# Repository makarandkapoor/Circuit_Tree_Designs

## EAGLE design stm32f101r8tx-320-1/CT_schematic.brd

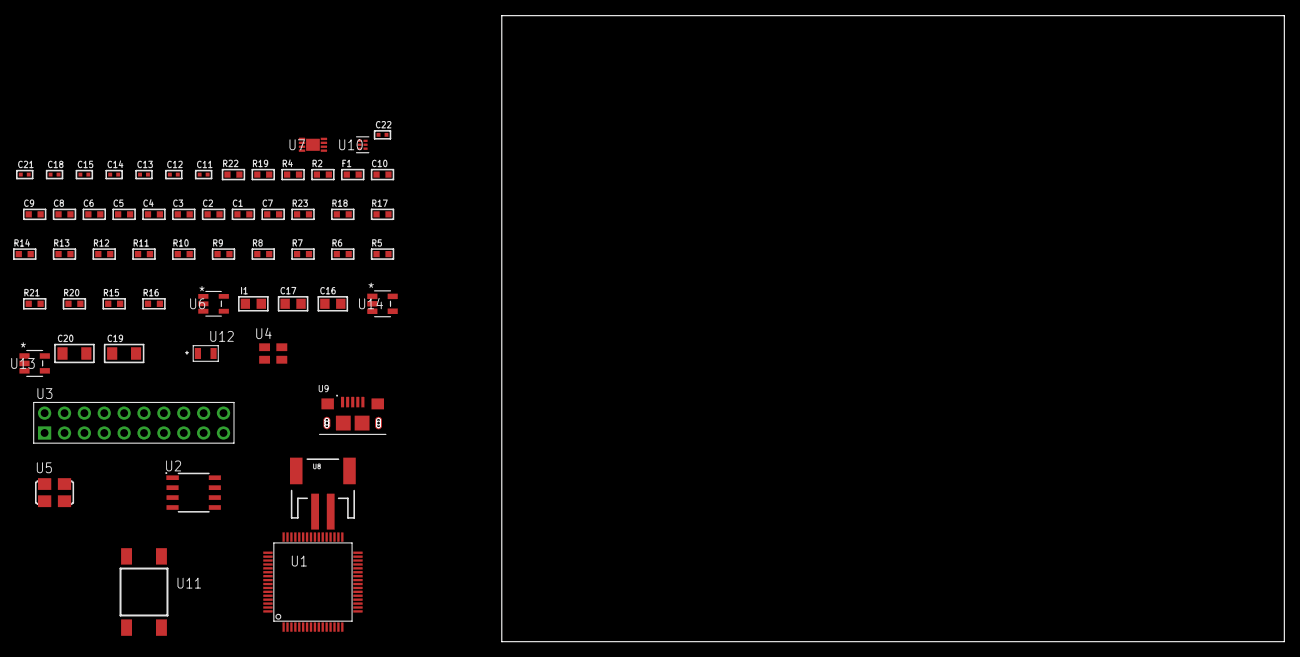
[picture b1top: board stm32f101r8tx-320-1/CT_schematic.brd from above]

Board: 2 copper layers, 122.6 x 80.0 mm, 59 parts (0 on the bottom side), 32 nets, no tracks yet.

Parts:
C1, C10: 1e-06; C0603
C2, C3, C4, C5, C6: 1e-07; C0603
C7: 4.7e-06; C0603
C8, C9: 1e-08; C0603
C11, C14, C15, C21, C22: 1e-08; C0402
C12, C13, C18: 1e-07; C0402
C16, C17: 1e-05; C0805
C19, C20: 1e-05; C1206
F1: 240.0; L0603
I1: 2.2e-06; L0805
R2: 1000.0; R0603
R4: 4700.0; R0603
R5, R6, R7, R8, R9, R10, R11, R12, R13, R14, R17, R18, R23: 10000.0; R0603
R15: 220000.0; R0603
R16: 1000000.0; R0603
R19: 9100.0; R0603
R20: 680000.0; R0603
R21: 120000.0; R0603
R22: 2000.0; R0603
U1: STM32F101R8T6; LQFP64
U2: AT25040B-SSHL-T; SOIC-8
U3: TST-110-05-T-D-RA
U4: ASEK-32.768KHz-ECST; ASEK
U5: ASFL1-25MHZ-NCS; ASFL1
U6: ltc3406es5; TSOT-23-5
U7: MCP73831T-2ACI/MC; DFN8_2X3MC
U8: S2B-PH-SM4-TB(LF)(SN); JST-2-SMD
U9: 10118193-0001LF; FCI_10118193-0001LF
U10: TPS3895ADRYR; SON-6
U11: 4-1437565-2; SW_4-1437565-2
U12: Q65110A2395; LGM67K-G1J2-24-Z
U13, U14: nc7sz125m5x; NC7SZ125M5X

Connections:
CLK_U1_3: U1.3, U4.3
CLK_U1_5: U1.5, U5.3
GND: C1.2, C2.2, C3.2, C4.2, C5.2, C6.2, C7.2, C8.2, C9.2, C10.2, C11.2, C12.2, C13.2, C14.2, C15.2, C16.2, C17.1, C17.2, C18.2, C19.2, C20.2, C21.2, C22.2, R2.2, R5.2, R14.2, R15.2, R19.2, R21.2, R22.2, U1.12, U1.18, U1.31, U1.47, U1.63, U2.4, U3.4, U3.6, U3.8, U3.10, U3.12, U3.14, U3.16, U3.18, U3.20, U4.2, U5.2, U6.2, U7.6, U7.9, U8.2, U9.5, U9.6, U9.7, U9.8, U9.9, U10.2, U12.C, U13.2, U13.3, U14.1, U14.3
INPUT_USBPOWER_5V: C19.1, R23.2, U7.1, U7.2, U9.1
NET_U1_7: R4.1, U1.7, U14.4
NET_U1_13: C8.1, C9.1, C10.1, F1.1, U1.13
NET_U1_60: R5.1, U1.60
NET_U1_62: U11.3, U11.4
NET_U2_3: R6.1, U2.3
NET_U2_7: R8.1, U2.7
NET_U3_3: R9.1, U3.3
NET_U3_7: R11.1, U3.7
NET_U3_9: R12.1, U3.9
NET_U3_19: R14.1, U3.19
NET_U6_3: I1.1, U6.3
NET_U6_5: R15.1, R16.1, U6.5
NET_U6_ATNET_3: I1.2, R16.2
NET_U7_5: R23.1, U7.5
NET_U7_8: R22.1, U7.8
NET_U10_1: R18.1, R19.1, U10.1
NET_U10_3: R20.2, R21.1, U10.3
NET_U10_4: R17.1, U10.4, U13.4, U14.2
NET_U11_1: R2.1, U11.1, U11.2
PROC_SPI1_MISO: U1.22, U2.2
PROC_SPI1_MOSI: U1.23, U2.5
PROC_SPI1_NSS: R7.1, U1.20, U2.1
PROC_SPI1_SCK: U1.21, U2.6
PROC_SYS_JTDI: R10.1, U1.50, U3.5
PROC_SYS_JTDO_TRACESWO: U1.55, U3.13
RST_OUT_U3_SRESET_B: R13.1, U3.15, U13.1
VCC_S1_3V7: C16.1, C20.1, U6.4, U7.3, U7.4, U8.1
VCC_TIER1_3V3: C1.1, C2.1, C3.1, C4.1, C5.1, C6.1, C7.1, C11.1, C12.1, C13.1, C14.1, C15.1, C17.2, C18.1, C21.1, C22.1, F1.2, I1.2, R4.2, R6.2, R7.2, R8.2, R9.2, R10.2, R11.2, R12.2, R13.2, R16.2, R17.2, R18.2, R20.1, U1.1, U1.19, U1.32, U1.48, U1.64, U2.8, U3.1, U3.2, U4.4, U5.4, U10.6, U13.5, U14.5

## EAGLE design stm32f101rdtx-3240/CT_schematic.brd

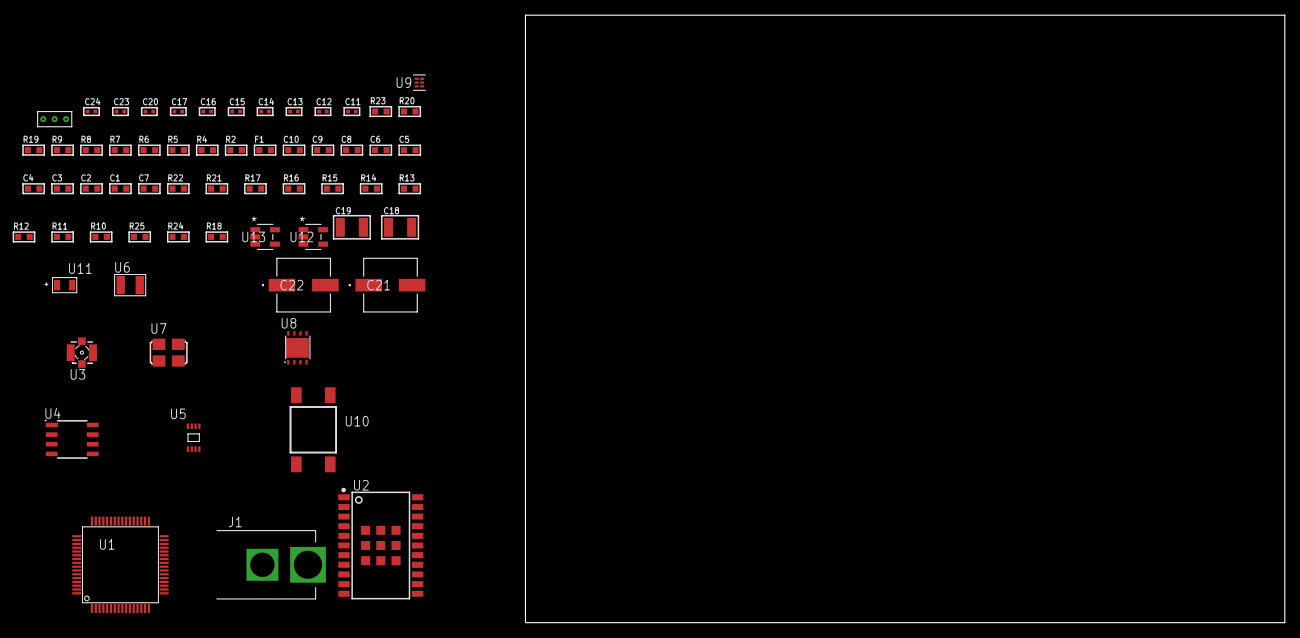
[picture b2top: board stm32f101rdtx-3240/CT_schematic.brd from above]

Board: 2 copper layers, 100.0 x 80.0 mm, 63 parts (0 on the bottom side), 37 nets, no tracks yet.

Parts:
C1, C10: 1e-06; C0603
C2, C3, C4, C5, C6: 1e-07; C0603
C7: 4.7e-06; C0603
C8, C9: 1e-08; C0603
C11, C12: 1e-11; C0402
C13, C20: 1e-07; C0402
C14, C15, C16, C17, C23, C24: 1e-08; C0402
C18, C19: 1e-05; C1210
C21, C22: 0.0001; EXV-9H
F1: 240.0; L0603
J1: PJ-037B; PJ-037B_PACKAGE
R2, R20: 1000.0; R0603
R4, R5: 4700.0; R0603
R6, R7, R8, R9: 2200.0; R0603
R10, R11, R12, R13, R14, R15, R16, R17, R21, R22: 10000.0; R0603
R18: 100000.0; R0603
R19: 2231.0; R0603
R23: 9100.0; R0603
R24: 680000.0; R0603
R25: 120000.0; R0603
U1: STM32F101RDT6; LQFP64
U2: A2200-A
U3: 73412-0114; COAXIAL_C
U4: AT25128B-SSHL-T; SOIC-8
U5: 24AA32AT-I/MNY; TDFN-8/6MM
U6: ABS07-32.768KHZ-7-T
U7: ASFL1-25MHZ-NCS; ASFL1
U8: LP3878SDX-ADJ/NOPB; WSON-8
U9: TPS3895ADRYR; SON-6
U10: 4-1437565-2; SW_4-1437565-2
U11: Q65110A2395; LGM67K-G1J2-24-Z
U12, U13: nc7sz125m5x; NC7SZ125M5X
U14: Dummy; DUMMY_PACKAGE_134

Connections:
CLK_CRYSTAL_U1_3: C11.1, U1.3, U6.1
CLK_CRYSTAL_U1_4: C12.1, U1.4, U6.2
CLK_U1_5: U1.5, U7.3
GND: C1.2, C2.2, C3.2, C4.2, C5.2, C6.2, C7.2, C8.2, C9.2, C10.2, C11.2, C12.2, C13.2, C14.2, C15.2, C16.2, C17.2, C18.2, C19.2, C20.2, C21.2, C22.2, C23.2, C24.2, J1.2, R2.2, R10.2, R17.2, R20.2, R23.2, R25.2, U1.12, U1.18, U1.31, U1.47, U1.63, U2.7, U2.8, U2.23, U2.24, U2.25, U2.26, U2.27, U2.28, U2.29, U2.30, U2.31, U4.4, U5.4, U5.7, U7.2, U8.3, U8.PAD, U9.2, U11.C, U12.1, U12.3, U13.1, U13.3, U14.1
NET_U1_7: R5.1, U1.7, U13.4
NET_U1_13: C8.1, C9.1, C10.1, F1.1, U1.13
NET_U1_29: R8.1, U1.29, U5.6
NET_U1_30: R9.1, U1.30, U5.5
NET_U1_58: R6.1, U1.58, U2.15
NET_U1_59: R7.1, U1.59, U2.16
NET_U1_60: R10.1, U1.60
NET_U1_62: U10.3, U10.4
NET_U2_2: R11.2, U2.2
NET_U2_17: R11.1, U2.17
NET_U2_22: R4.1, U2.22, U12.4
NET_U3_1: U2.11, U3.1
NET_U3_2: U2.10, U3.2, U3.3, U3.4
NET_U4_3: R12.1, U4.3
NET_U4_7: R14.1, U4.7
NET_U5_1: R15.1, U5.1
NET_U5_2: R16.1, U5.2
NET_U5_3: R17.1, U5.3
NET_U8_1: C17.1, U8.1
NET_U8_6: R19.2, R20.1, U8.6
NET_U8_8: R18.1, U8.8
NET_U9_1: R22.1, R23.1, U9.1
NET_U9_3: R24.2, R25.1, U9.3
NET_U9_4: R21.1, U9.4, U12.2, U13.2
NET_U10_1: R2.1, U10.1, U10.2
PROC_SPI1_MISO: U1.22, U4.2
PROC_SPI1_MOSI: U1.23, U4.5
PROC_SPI1_NSS: R13.1, U1.20, U4.1
PROC_SPI1_SCK: U1.21, U4.6
PROC_TIM2_CH3: U1.16, U14.3
PROC_TIM2_CH4: U1.17, U14.2
VCC_S1_13V9: C18.1, C21.1, C22.1, J1.1, R18.2, U8.4
VCC_TIER1_3V3: C1.1, C2.1, C3.1, C4.1, C5.1, C6.1, C7.1, C13.1, C14.1, C15.1, C16.1, C19.1, C20.1, C23.1, C24.1, F1.2, R4.2, R5.2, R6.2, R7.2, R8.2, R9.2, R12.2, R13.2, R14.2, R15.2, R16.2, R19.1, R21.2, R22.2, R24.1, U1.1, U1.19, U1.32, U1.48, U1.64, U2.20, U4.8, U5.8, U7.4, U8.5, U9.6, U12.5, U13.5

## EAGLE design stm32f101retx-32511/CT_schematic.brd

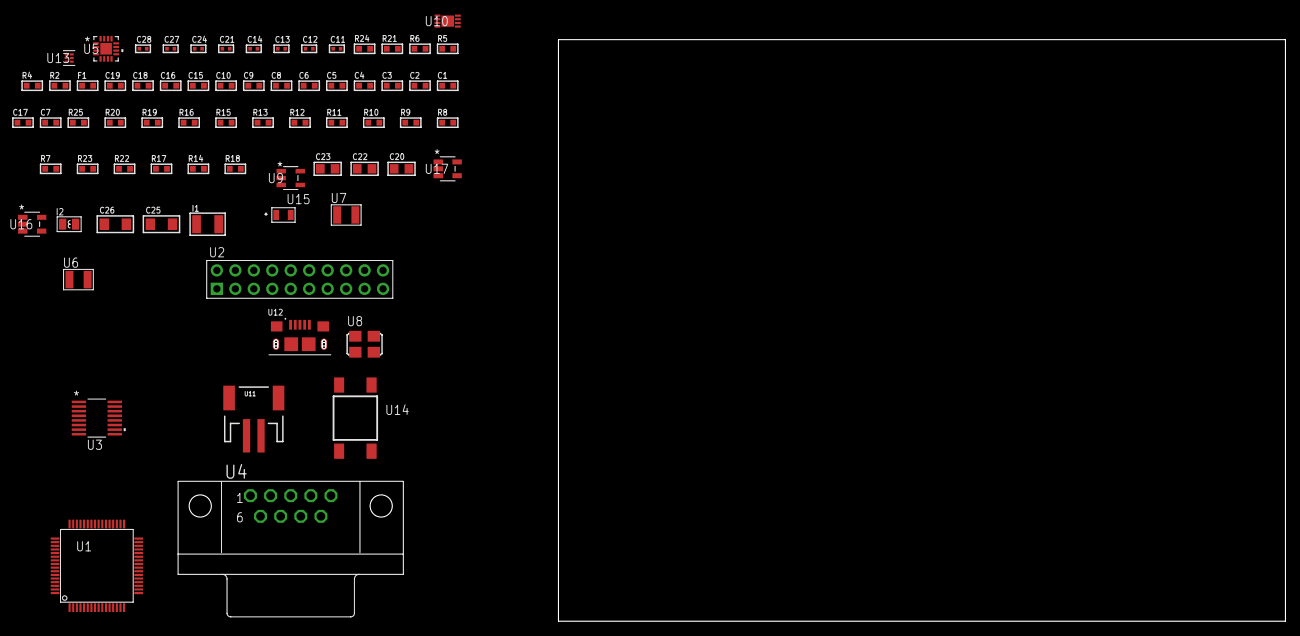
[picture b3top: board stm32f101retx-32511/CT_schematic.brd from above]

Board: 2 copper layers, 71 parts (0 on the bottom side), 44 nets, no tracks yet.

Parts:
C1, C10, C15, C16, C18, C19: 1e-06; C0603
C2, C3, C4, C5, C6: 1e-07; C0603
C7: 4.7e-06; C0603
C8, C9: 1e-08; C0603
C11, C12: 1e-11; C0402
C13, C14, C24: 1e-07; C0402
C17: 2.2e-07; C0603
C20: 4.7e-06; C0805
C21, C27, C28: 1e-08; C0402
C22, C23: 1e-05; C0805
C25, C26: 1e-05; C1206
F1: 240.0; L0603
I1: 1e-05; L1210
I2: 1.5e-06; L0806
R2: 1000.0; R0603
R4: 4700.0; R0603
R5, R6: 2200.0; R0603
R7, R8, R9, R10, R11, R12, R13, R15, R16, R19, R20, R25: 10000.0; R0603
R14: 100000.0; R0603
R17: 220000.0; R0603
R18: 1000000.0; R0603
R21: 9100.0; R0603
R22: 680000.0; R0603
R23: 120000.0; R0603
R24: 2000.0; R0603
U1: STM32F101RET6; LQFP64
U2: TST-110-05-T-D-RA
U3: LTC2804CGN-1#PBF; SSOP-16
U4: 182-009-113R531; 182-009-MALE
U5: M41T65Q6F; M41T65_QFN-16
U6, U7: ABS07-32.768KHZ-7-T
U8: ASFL1-25MHZ-NCS; ASFL1
U9: ltc3406es5; TSOT-23-5
U10: MCP73831T-2ACI/MC; DFN8_2X3MC
U11: S2B-PH-SM4-TB(LF)(SN); JST-2-SMD
U12: 10118193-0001LF; FCI_10118193-0001LF
U13: TPS3895ADRYR; SON-6
U14: 4-1437565-2; SW_4-1437565-2
U15: Q65110A2395; LGM67K-G1J2-24-Z
U16, U17: nc7sz125m5x; NC7SZ125M5X

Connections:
CLK_CRYSTAL_U1_3: C11.1, U1.3, U7.1
CLK_CRYSTAL_U1_4: C12.1, U1.4, U7.2
CLK_CRYSTAL_U5_1: U5.1, U6.1
CLK_CRYSTAL_U5_2: U5.2, U6.2
CLK_U1_5: U1.5, U8.3
GND: C1.2, C2.2, C3.2, C4.2, C5.2, C6.2, C7.2, C8.2, C9.2, C10.2, C11.2, C12.2, C13.2, C14.2, C15.2, C16.2, C18.2, C19.2, C20.2, C21.2, C22.2, C23.1, C23.2, C24.2, C25.2, C26.2, C27.2, C28.2, R2.2, R7.2, R13.2, R17.2, R21.2, R23.2, R24.2, U1.12, U1.18, U1.31, U1.47, U1.63, U2.4, U2.6, U2.8, U2.10, U2.12, U2.14, U2.16, U2.18, U2.20, U3.8, U4.5, U5.3, U5.5, U5.17, U8.2, U9.2, U10.6, U10.9, U11.2, U12.5, U12.6, U12.7, U12.8, U12.9, U13.2, U15.C, U16.2, U16.3, U17.1, U17.3
INPUT_USBPOWER_5V: C25.1, R25.2, U10.1, U10.2, U12.1
NET_U1_7: R4.1, U1.7, U17.4
NET_U1_13: C8.1, C9.1, C10.1, F1.1, U1.13
NET_U1_58: R5.1, U1.58, U5.10
NET_U1_59: R6.1, U1.59, U5.9
NET_U1_60: R7.1, U1.60
NET_U1_62: U14.3, U14.4
NET_U2_3: R8.1, U2.3
NET_U2_7: R10.1, U2.7
NET_U2_9: R11.1, U2.9
NET_U2_19: R13.1, U2.19
NET_U3_6: C15.1, U3.6
NET_U3_7: C17.1, I1.2, U3.7
NET_U3_9: C16.1, U3.9
NET_U3_10: C17.2, U3.10
NET_U3_11: R14.1, U3.11
NET_U4_2: U3.1, U4.2
NET_U4_3: U3.3, U4.3
NET_U4_7: U3.2, U4.7
NET_U4_8: U3.4, U4.8
NET_U5_4: R15.1, U5.4
NET_U5_11: R16.1, U5.11
NET_U9_3: I2.1, U9.3
NET_U9_5: R17.1, R18.1, U9.5
NET_U9_ATNET_3: I2.2, R18.2
NET_U10_5: R25.1, U10.5
NET_U10_8: R24.1, U10.8
NET_U13_1: R20.1, R21.1, U13.1
NET_U13_3: R22.2, R23.1, U13.3
NET_U13_4: R19.1, U13.4, U16.4, U17.2
NET_U14_1: R2.1, U14.1, U14.2
PROC_SYS_JTDI: R9.1, U1.50, U2.5
PROC_SYS_JTDO_TRACESWO: U1.55, U2.13
PROC_UART4_RX: U1.52, U3.16
PROC_UART4_TX: U1.51, U3.14
RST_OUT_U2_SRESET_B: R12.1, U2.15, U16.1
VCC_S1_3V7: C22.1, C26.1, U9.4, U10.3, U10.4, U11.1
VCC_TIER1_3V3: C1.1, C2.1, C3.1, C4.1, C5.1, C6.1, C7.1, C13.1, C14.1, C18.1, C19.1, C20.1, C21.1, C23.2, C24.1, C27.1, C28.1, F1.2, I1.1, I2.2, R4.2, R5.2, R6.2, R8.2, R9.2, R10.2, R11.2, R12.2, R14.2, R15.2, R16.2, R18.2, R19.2, R20.2, R22.1, U1.1, U1.19, U1.32, U1.48, U1.64, U2.1, U2.2, U3.5, U3.12, U5.14, U8.4, U13.6, U16.5, U17.5

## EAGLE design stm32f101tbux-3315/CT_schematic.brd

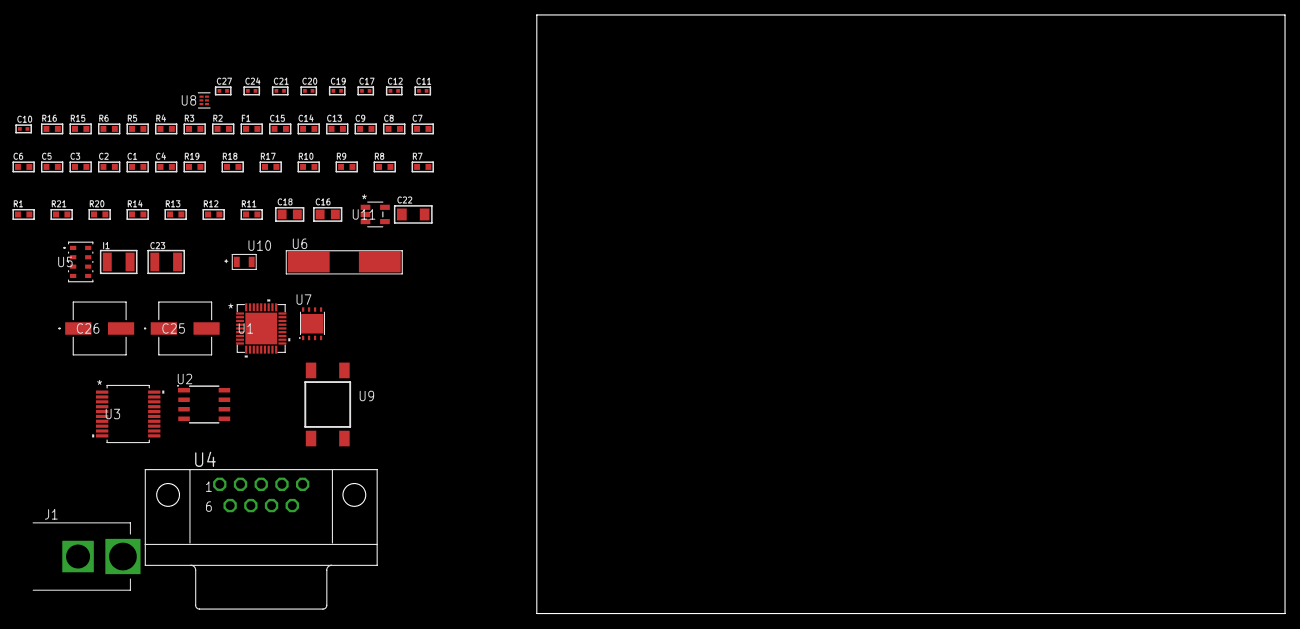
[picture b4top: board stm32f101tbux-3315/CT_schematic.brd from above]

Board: 2 copper layers, 100.0 x 80.0 mm, 62 parts (0 on the bottom side), 41 nets, no tracks yet.

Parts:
C1, C2, C3, C5, C6: 1e-07; C0603
C4: 4.7e-06; C0603
C7, C8: 1e-08; C0603
C9, C13, C14, C15: 1e-06; C0603
C10, C11: 1e-11; C0402
C12, C21, C27: 1e-08; C0402
C16: 4.7e-06; C0805
C17, C19, C20, C24: 1e-07; C0402
C18: 1e-05; C0805
C22: 1e-05; C1206
C23: 1e-05; C1210
C25, C26: 0.0001; EXV-9H
F1: 240.0; L0603
I1: 1.5e-05; L1210
J1: PJ-037B; PJ-037B_PACKAGE
R1, R7, R8, R9, R10, R17, R18: 10000.0; R0603
R2, R16: 1000.0; R0603
R3: 1270.0; R0603
R4: 4700.0; R0603
R5, R6: 2200.0; R0603
R11, R12, R13, R14: 100000.0; R0603
R15: 1500.0; R0603
R19: 18000.0; R0603
R20: 470000.0; R0603
R21: 120000.0; R0603
U1: STM32F101TBU6; VFQFPN36
U2: AT25128B-SSHL-T; SOIC-8
U3: MAX3218EAP+T; SSOP-20
U4: 182-009-113R531; 182-009-MALE
U5: MPL3115A2R1; LGA-8
U6: ABLS-25.000MHZ-B2F-T
U7: LP3878SDX-ADJ/NOPB; WSON-8
U8: TPS3895ADRYR; SON-6
U9: 4-1437565-2; SW_4-1437565-2
U10: Q65110A2395; LGM67K-G1J2-24-Z
U11: nc7sz125m5x; NC7SZ125M5X

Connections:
CLK_CRYSTAL_U1_2: C10.1, U1.2, U6.1
CLK_CRYSTAL_U1_3: C11.1, U1.3, U6.2
GND: C1.2, C2.2, C3.2, C4.2, C5.2, C6.2, C7.2, C8.2, C9.2, C10.2, C11.2, C12.2, C13.2, C14.2, C15.2, C17.2, C18.2, C19.2, C20.2, C21.2, C22.2, C23.2, C24.2, C25.2, C26.2, C27.2, J1.2, R2.2, R7.2, R16.2, R19.2, R21.2, U1.5, U1.18, U1.26, U1.36, U1.37, U2.4, U3.5, U3.17, U3.20, U4.5, U5.3, U7.3, U7.PAD, U8.2, U10.C, U11.1, U11.3
NET_U1_4: R4.1, U1.4, U11.4
NET_U1_6: C7.1, C8.1, C9.1, F1.1, U1.6
NET_U1_31: R3.1, U1.31, U10.A
NET_U1_32: R1.1, U1.32, U9.3, U9.4
NET_U1_33: R5.1, U1.33, U5.8
NET_U1_34: R6.1, U1.34, U5.7
NET_U1_35: R7.1, U1.35
NET_U2_3: R8.1, U2.3
NET_U2_7: R10.1, U2.7
NET_U3_1: I1.1, U3.1
NET_U3_2: R11.1, U3.2
NET_U3_3: R12.1, U3.3
NET_U3_4: R13.1, U3.4
NET_U3_15: C15.1, U3.15
NET_U3_16: C16.2, U3.16
NET_U3_18: C16.1, U3.18
NET_U3_19: C14.1, U3.19
NET_U4_2: U3.12, U4.2
NET_U4_3: U3.14, U4.3
NET_U4_7: U3.11, U4.7
NET_U4_8: U3.13, U4.8
NET_U5_2: C20.1, U5.2
NET_U7_1: C21.1, U7.1
NET_U7_6: R15.2, R16.1, U7.6
NET_U7_8: R14.1, U7.8
NET_U8_1: R18.1, R19.1, U8.1
NET_U8_3: R20.2, R21.1, U8.3
NET_U8_4: R17.1, U8.4, U11.2
NET_U9_1: R2.1, U9.1, U9.2
PROC_SPI1_MISO: U1.13, U2.2
PROC_SPI1_MOSI: U1.14, U2.5
PROC_SPI1_NSS: R9.1, U1.11, U2.1
PROC_SPI1_SCK: U1.12, U2.6
PROC_USART1_CTS: U1.23, U3.8
PROC_USART1_RX: U1.22, U3.9
PROC_USART1_TX: U1.21, U3.7
VCC_S1_9V8: C22.1, C25.1, C26.1, J1.1, R14.2, U7.4
VCC_TIER1_2V5: C1.1, C2.1, C3.1, C4.1, C5.1, C6.1, C12.1, C13.1, C17.1, C18.1, C19.1, C23.1, C24.1, C27.1, F1.2, I1.2, R1.2, R3.2, R4.2, R5.2, R6.2, R8.2, R9.2, R10.2, R11.2, R12.2, R13.2, R15.1, R17.2, R18.2, R20.1, U1.1, U1.19, U1.27, U2.8, U3.6, U5.1, U5.4, U7.5, U8.6, U11.5

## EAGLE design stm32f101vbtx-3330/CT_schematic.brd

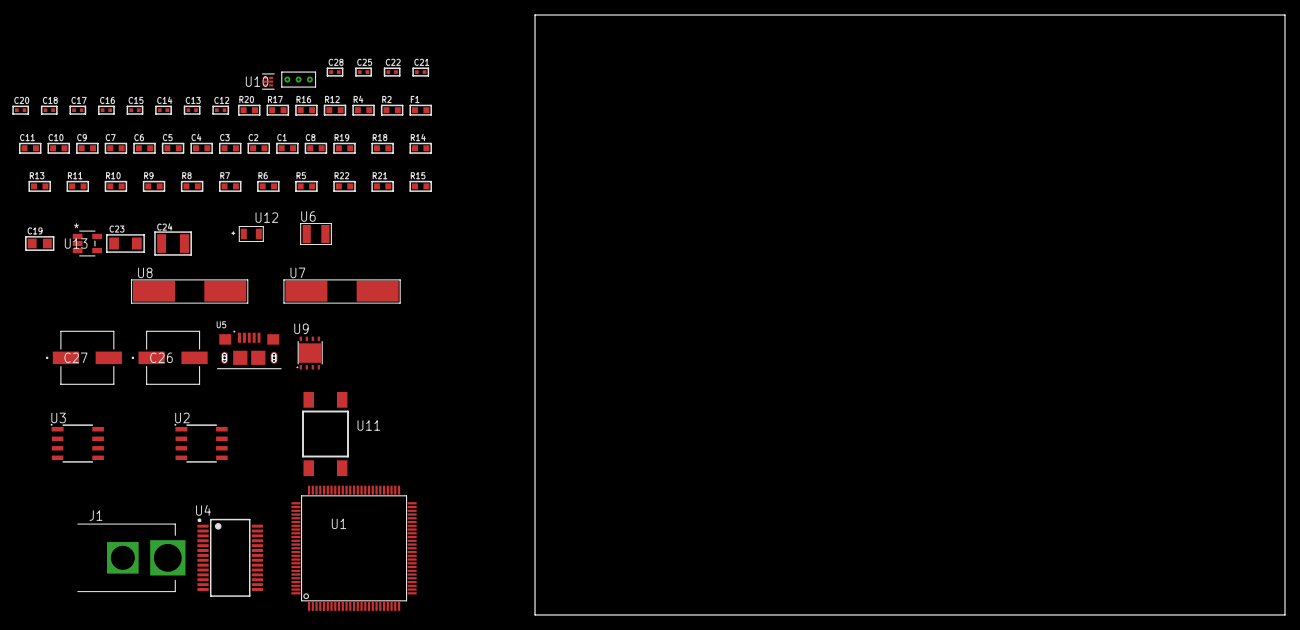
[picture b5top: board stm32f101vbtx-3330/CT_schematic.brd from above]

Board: 2 copper layers, 64 parts (0 on the bottom side), 43 nets, no tracks yet.

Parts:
C1, C11: 1e-06; C0603
C2, C3, C4, C5, C6, C7: 1e-07; C0603
C8: 4.7e-06; C0603
C9, C10: 1e-08; C0603
C12, C13, C14, C15: 1e-11; C0402
C16, C17, C22, C28: 1e-08; C0402
C18, C20, C21, C25: 1e-07; C0402
C19: 4.7e-06; C0805
C23: 1e-05; C1206
C24: 1e-05; C1210
C26, C27: 0.0001; EXV-9H
F1: 240.0; L0603
J1: PJ-037B; PJ-037B_PACKAGE
R2, R17: 1000.0; R0603
R4, R12: 4700.0; R0603
R5, R6, R7, R8, R9, R10, R11, R13, R14, R18, R19: 10000.0; R0603
R15: 100000.0; R0603
R16: 2231.0; R0603
R20: 9100.0; R0603
R21: 680000.0; R0603
R22: 120000.0; R0603
U1: STM32F101VBT6; LQFP100
U2: AT25160B-SSHL-T; SOIC-8
U3: AT25640B-SSHL-T; SOIC-8
U4: FT232RL-REEL; SSOP-28
U5: 10118193-0001LF; FCI_10118193-0001LF
U6: ABS07-32.768KHZ-7-T
U7: ABLS-25.000MHZ-B2F-T
U8: ABLS-12.000MHZ-B4-T
U9: LP3878SDX-ADJ/NOPB; WSON-8
U10: TPS3895ADRYR; SON-6
U11: 4-1437565-2; SW_4-1437565-2
U12: Q65110A2395; LGM67K-G1J2-24-Z
U13: nc7sz125m5x; NC7SZ125M5X
U14: Dummy; DUMMY_PACKAGE_136

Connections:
CLK_CRYSTAL_U1_8: C12.1, U1.8, U6.1
CLK_CRYSTAL_U1_9: C13.1, U1.9, U6.2
CLK_CRYSTAL_U1_12: C14.1, U1.12, U7.1
CLK_CRYSTAL_U1_13: C15.1, U1.13, U7.2
CLK_CRYSTAL_U4_27: U4.27, U8.1
CLK_CRYSTAL_U4_28: U4.28, U8.2
GND: C1.2, C2.2, C3.2, C4.2, C5.2, C6.2, C7.2, C8.2, C9.2, C10.2, C11.2, C12.2, C13.2, C14.2, C15.2, C16.2, C17.2, C18.2, C19.2, C20.2, C21.2, C22.2, C23.2, C24.2, C25.2, C26.2, C27.2, C28.2, J1.2, R2.2, R5.2, R14.2, R17.2, R20.2, R22.2, U1.10, U1.19, U1.20, U1.27, U1.49, U1.74, U1.99, U2.4, U3.4, U4.7, U4.18, U4.21, U4.25, U4.26, U5.5, U5.6, U5.7, U5.8, U5.9, U9.3, U9.PAD, U10.2, U12.C, U13.1, U13.3, U14.1
NET_U1_14: R4.1, U1.14, U13.4
NET_U1_22: C9.1, C10.1, C11.1, F1.1, U1.21, U1.22
NET_U1_94: R5.1, U1.94
NET_U1_98: U11.3, U11.4
NET_U2_3: R6.1, U2.3
NET_U2_7: R8.1, U2.7
NET_U3_3: R9.1, U3.3
NET_U3_7: R11.1, U3.7
NET_U4_14: R13.1, U4.14
NET_U4_17: C20.1, U4.17
NET_U4_19: R14.1, U4.19
NET_U5_1: R12.1, U5.1
NET_U5_2: U4.16, U5.2
NET_U5_3: U4.15, U5.3
NET_U9_1: C22.1, U9.1
NET_U9_6: R16.2, R17.1, U9.6
NET_U9_8: R15.1, U9.8
NET_U10_1: R19.1, R20.1, U10.1
NET_U10_3: R21.2, R22.1, U10.3
NET_U10_4: R18.1, U10.4, U13.2
NET_U11_1: R2.1, U11.1, U11.2
PROC_ADC1_IN2: U1.25, U14.3
PROC_ADC1_IN3: U1.26, U14.2
PROC_SPI1_MISO: U1.31, U3.2
PROC_SPI1_MOSI: U1.32, U3.5
PROC_SPI1_NSS: R10.1, U1.29, U3.1
PROC_SPI1_SCK: U1.30, U3.6
PROC_SPI2_MISO: U1.53, U2.2
PROC_SPI2_MOSI: U1.54, U2.5
PROC_SPI2_NSS: R7.1, U1.51, U2.1
PROC_SPI2_SCK: U1.52, U2.6
PROC_USART1_CTS: U1.70, U4.3
PROC_USART1_RX: U1.69, U4.1
PROC_USART1_TX: U1.68, U4.5
VCC_S1_8V2: C23.1, C26.1, C27.1, J1.1, R15.2, U9.4
VCC_TIER1_3V3: C1.1, C2.1, C3.1, C4.1, C5.1, C6.1, C7.1, C8.1, C16.1, C17.1, C18.1, C19.1, C21.1, C24.1, C25.1, C28.1, F1.2, R4.2, R6.2, R7.2, R8.2, R9.2, R10.2, R11.2, R13.2, R16.1, R18.2, R19.2, R21.1, U1.6, U1.11, U1.28, U1.50, U1.75, U1.100, U2.8, U3.8, U4.4, U4.20, U9.5, U10.6, U13.5

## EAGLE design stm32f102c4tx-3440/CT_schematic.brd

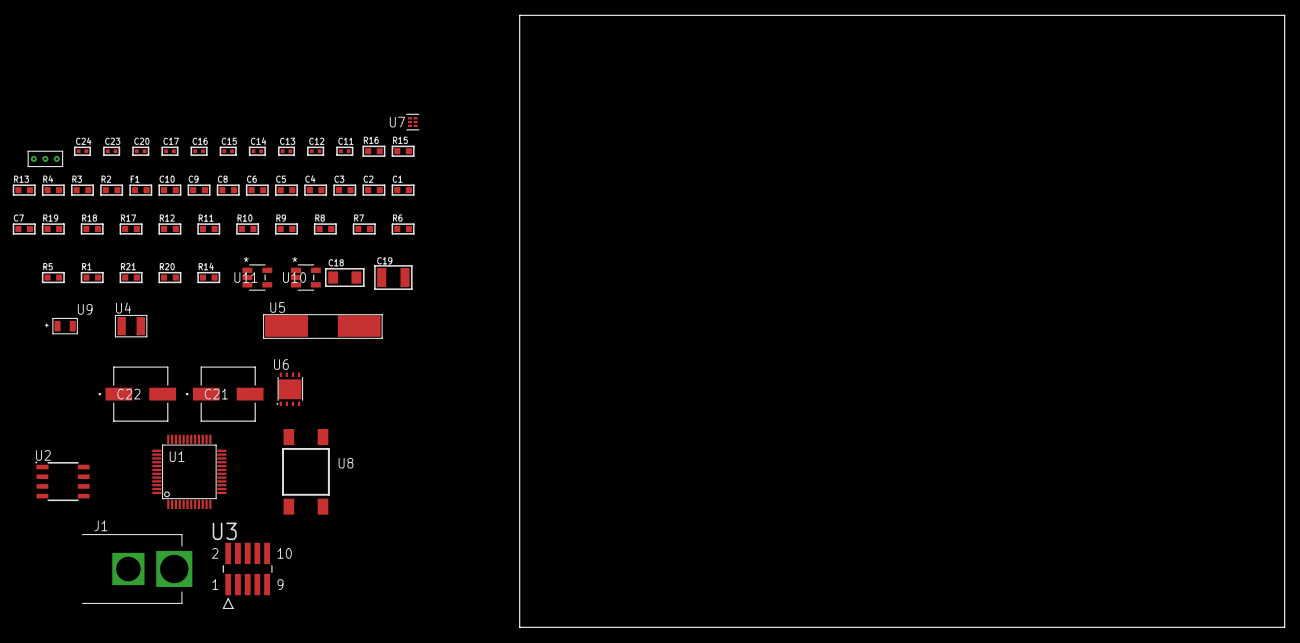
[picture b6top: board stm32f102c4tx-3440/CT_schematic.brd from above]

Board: 2 copper layers, 100.0 x 80.0 mm, 59 parts (0 on the bottom side), 33 nets, no tracks yet.

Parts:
C1, C10: 1e-06; C0603
C2, C3, C4, C5, C6: 1e-07; C0603
C7: 4.7e-06; C0603
C8, C9: 1e-08; C0603
C11, C12, C13, C14: 1e-11; C0402
C15, C17, C23, C24: 1e-08; C0402
C16, C20: 1e-07; C0402
C18: 1e-05; C1206
C19: 1e-05; C1210
C21, C22: 0.0001; EXV-9H
F1: 240.0; L0603
J1: PJ-037B; PJ-037B_PACKAGE
R1, R5, R6, R7, R8, R9, R10, R11, R12, R17, R18: 10000.0; R0603
R2, R16: 1000.0; R0603
R3: 1270.0; R0603
R4: 4700.0; R0603
R13: 5.0; R0603
R14: 100000.0; R0603
R15: 1500.0; R0603
R19: 18000.0; R0603
R20: 470000.0; R0603
R21: 120000.0; R0603
U1: STM32F102C4T6; LQFP48
U2: AT25080B-SSHL-T; SOIC-8
U3: FTSH-105-01-L-DV-K; SAMTEC_FTSH-105-01-L-DV-K
U4: ABS07-32.768KHZ-7-T
U5: ABLS-25.000MHZ-B2F-T
U6: LP3878SDX-ADJ/NOPB; WSON-8
U7: TPS3895ADRYR; SON-6
U8: 4-1437565-2; SW_4-1437565-2
U9: Q65110A2395; LGM67K-G1J2-24-Z
U10, U11: nc7sz125m5x; NC7SZ125M5X
U12: Dummy; DUMMY_PACKAGE_118

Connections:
CLK_CRYSTAL_U1_3: C11.1, U1.3, U4.1
CLK_CRYSTAL_U1_4: C12.1, U1.4, U4.2
CLK_CRYSTAL_U1_5: C13.1, U1.5, U5.1
CLK_CRYSTAL_U1_6: C14.1, U1.6, U5.2
GND: C1.2, C2.2, C3.2, C4.2, C5.2, C6.2, C7.2, C8.2, C9.2, C10.2, C11.2, C12.2, C13.2, C14.2, C15.2, C16.2, C17.2, C18.2, C19.2, C20.2, C21.2, C22.2, C23.2, C24.2, J1.2, R2.2, R5.2, R12.2, R13.2, R16.2, R19.2, R21.2, U1.8, U1.23, U1.35, U1.47, U2.4, U3.3, U3.5, U6.3, U6.PAD, U7.2, U9.C, U10.2, U10.3, U11.1, U11.3, U12.1
NET_U1_7: R4.1, U1.7, U11.4
NET_U1_9: C8.1, C9.1, C10.1, F1.1, U1.9
NET_U1_44: R5.1, U1.44
NET_U1_45: R3.1, U1.45, U9.A
NET_U1_46: R1.1, U1.46, U8.3, U8.4
NET_U2_3: R6.1, U2.3
NET_U2_7: R8.1, U2.7
NET_U3_2: R11.1, U3.2
NET_U3_4: R12.1, U3.4
NET_U3_9: R13.1, U3.9
NET_U6_1: C17.1, U6.1
NET_U6_6: R15.2, R16.1, U6.6
NET_U6_8: R14.1, U6.8
NET_U7_1: R18.1, R19.1, U7.1
NET_U7_3: R20.2, R21.1, U7.3
NET_U7_4: R17.1, U7.4, U10.4, U11.2
NET_U8_1: R2.1, U8.1, U8.2
PROC_SPI1_MISO: U1.16, U2.2
PROC_SPI1_MOSI: U1.17, U2.5
PROC_SPI1_NSS: R7.1, U1.14, U2.1
PROC_SPI1_SCK: U1.15, U2.6
PROC_SYS_JTDI: R10.1, U1.38, U3.8
PROC_SYS_JTDO_TRACESWO: U1.39, U3.6
PROC_TIM2_CH3: U1.12, U12.3
PROC_TIM2_CH4: U1.13, U12.2
RST_OUT_U3_JTAG_RST_B: R9.1, U3.10, U10.1
VCC_S1_8V1: C18.1, C21.1, C22.1, J1.1, R14.2, U6.4
VCC_TIER1_2V5: C1.1, C2.1, C3.1, C4.1, C5.1, C6.1, C7.1, C15.1, C16.1, C19.1, C20.1, C23.1, C24.1, F1.2, R1.2, R3.2, R4.2, R6.2, R7.2, R8.2, R9.2, R10.2, R11.2, R15.1, R17.2, R18.2, R20.1, U1.1, U1.24, U1.36, U1.48, U2.8, U3.1, U6.5, U7.6, U10.5, U11.5

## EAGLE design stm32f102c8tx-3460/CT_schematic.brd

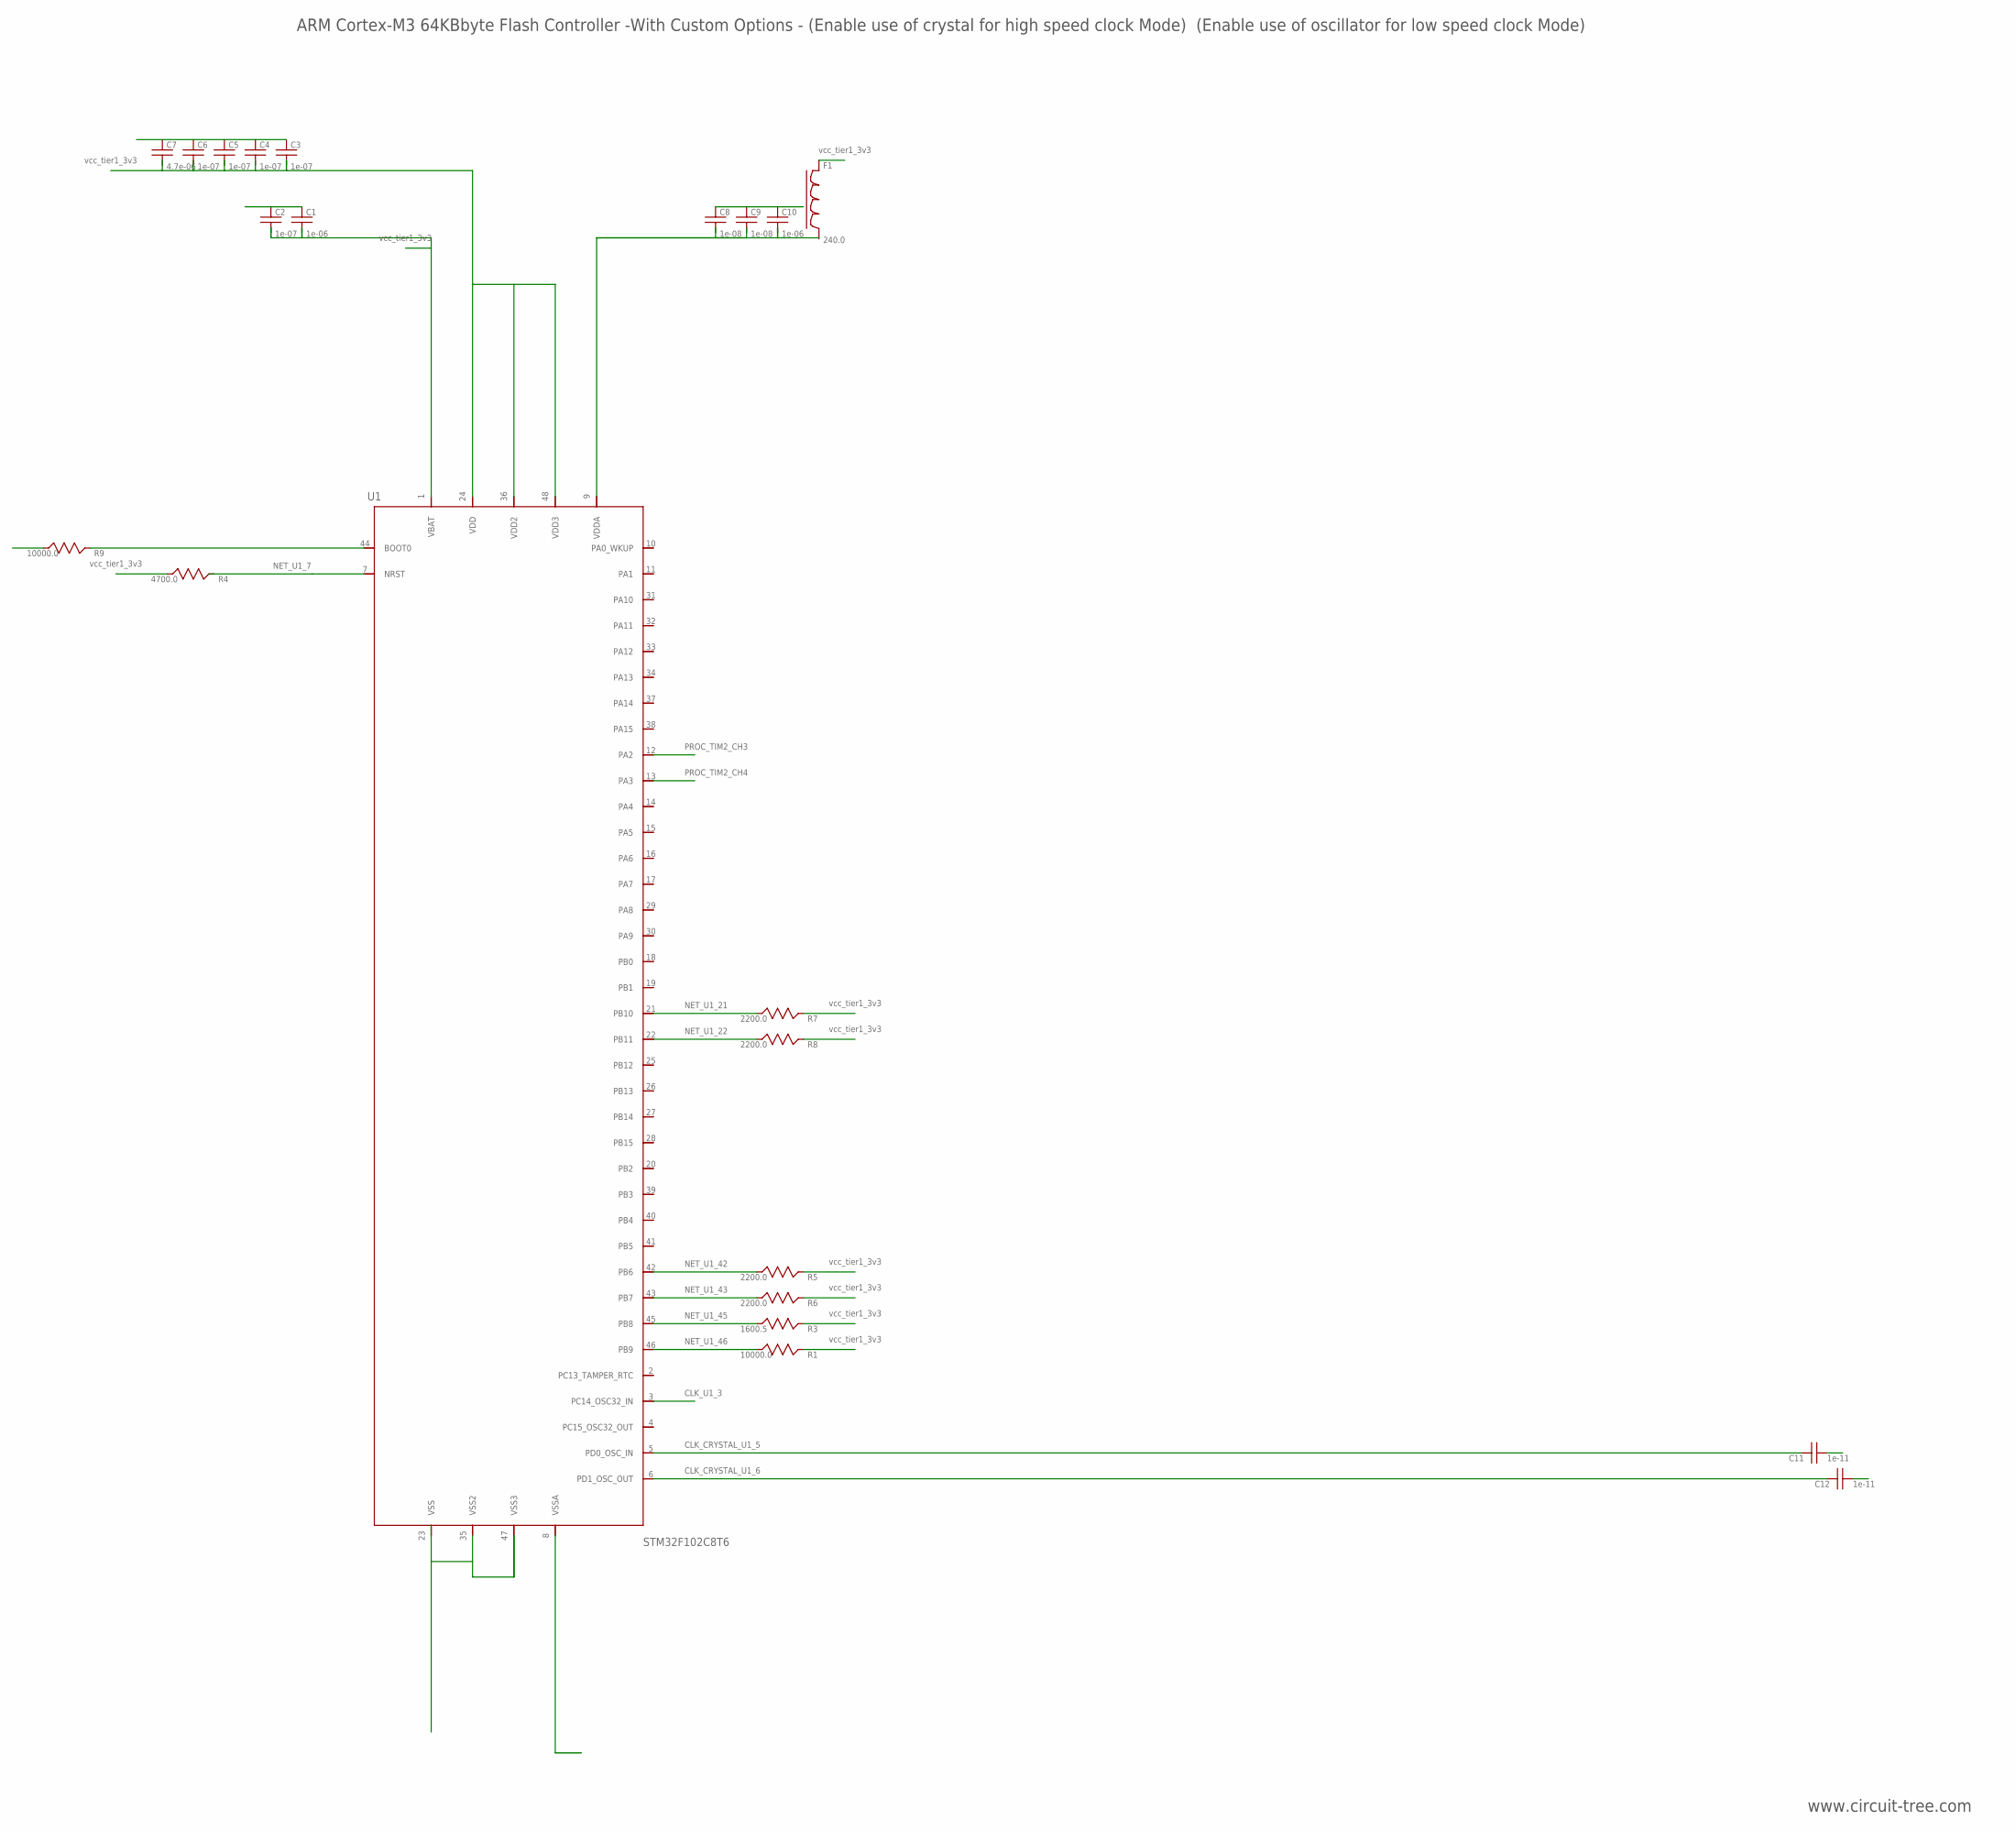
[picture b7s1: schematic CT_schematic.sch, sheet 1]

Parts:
C1, C10: 1e-06; C0603
C2, C3, C4, C5, C6: 1e-07; C0603
C7: 4.7e-06; C0603
C8, C9: 1e-08; C0603
C11, C12: 1e-11; C0402
F1: 240.0; L0603
R1, R9: 10000.0; R0603
R3: 1600.5; R0603
R4: 4700.0; R0603
R5, R6, R7, R8: 2200.0; R0603
U1: STM32F102C8T6; LQFP48

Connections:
CLK_CRYSTAL_U1_5: C11.1, U1.5 (PD0_OSC_IN); also elsewhere on the board
CLK_CRYSTAL_U1_6: C12.1, U1.6 (PD1_OSC_OUT); also elsewhere on the board
CLK_U1_3: U1.3 (PC14_OSC32_IN); also elsewhere on the board
GND: C1.2, C2.2, C3.2, C4.2, C5.2, C6.2, C7.2, C8.2, C9.2, C10.2, C11.2, C12.2, R9.2, U1.8 (VSSA), U1.23 (VSS), U1.35 (VSS2), U1.47 (VSS3); also elsewhere on the board
NET_U1_7: R4.1, U1.7 (NRST); also elsewhere on the board
NET_U1_9: C8.1, C9.1, C10.1, F1.1, U1.9 (VDDA)
NET_U1_21: R7.1, U1.21 (PB10); also elsewhere on the board
NET_U1_22: R8.1, U1.22 (PB11); also elsewhere on the board
NET_U1_42: R5.1, U1.42 (PB6); also elsewhere on the board
NET_U1_43: R6.1, U1.43 (PB7); also elsewhere on the board
NET_U1_44: R9.1, U1.44 (BOOT0)
NET_U1_45: R3.1, U1.45 (PB8); also elsewhere on the board
NET_U1_46: R1.1, U1.46 (PB9); also elsewhere on the board
PROC_TIM2_CH3: U1.12 (PA2); also elsewhere on the board
PROC_TIM2_CH4: U1.13 (PA3); also elsewhere on the board
VCC_TIER1_3V3: C1.1, C2.1, C3.1, C4.1, C5.1, C6.1, C7.1, F1.2, R1.2, R3.2, R4.2, R5.2, R6.2, R7.2, R8.2, U1.1 (VBAT), U1.24 (VDD), U1.36 (VDD2), U1.48 (VDD3); also elsewhere on the board

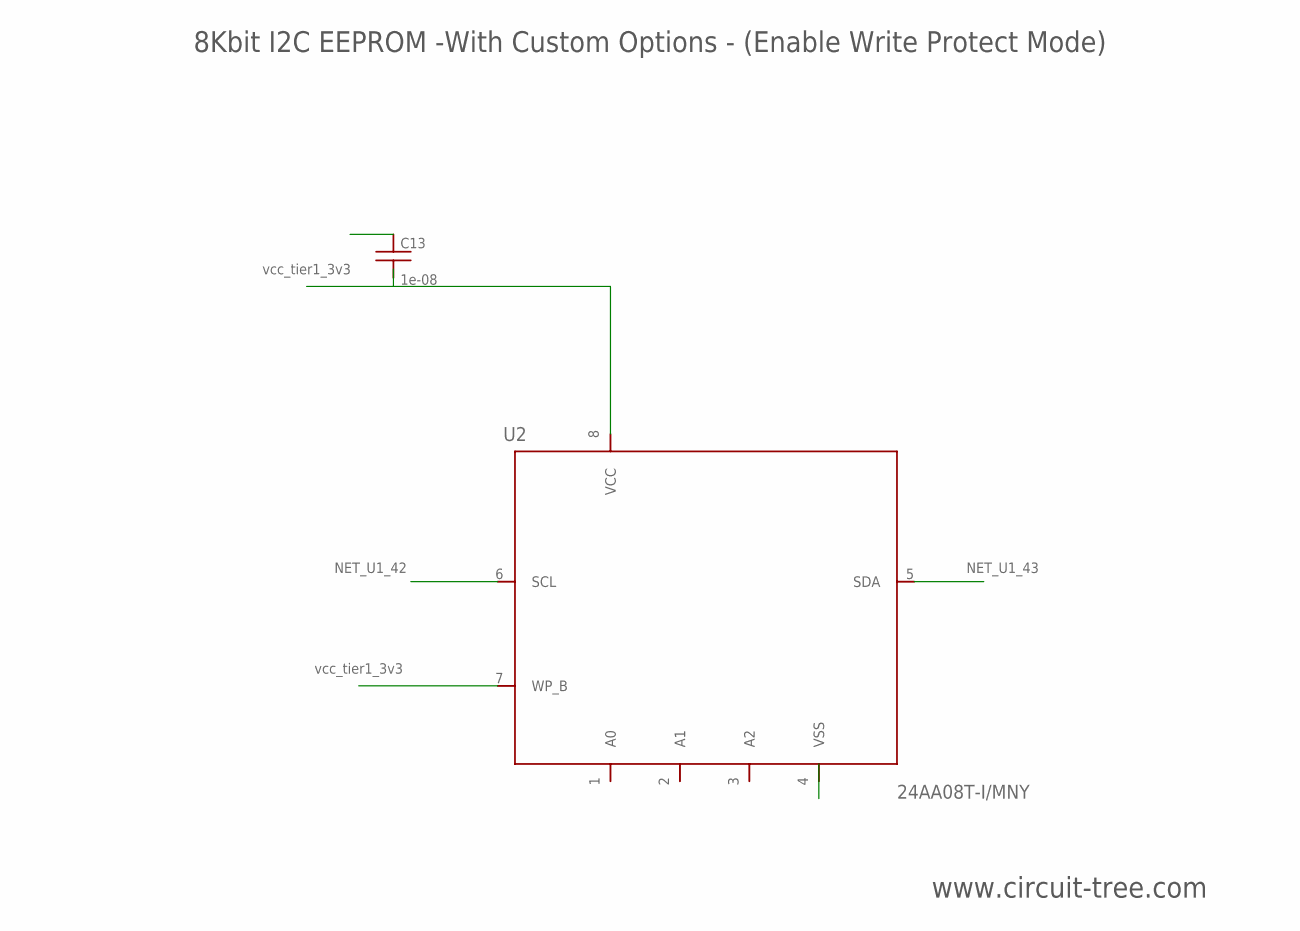
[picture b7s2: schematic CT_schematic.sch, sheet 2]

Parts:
C13: 1e-08; C0402
U2: 24AA08T-I/MNY; TDFN-8/6MM

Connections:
GND: C13.2, U2.4 (VSS); also elsewhere on the board
NET_U1_42: U2.6 (SCL); also elsewhere on the board
NET_U1_43: U2.5 (SDA); also elsewhere on the board
VCC_TIER1_3V3: C13.1, U2.7 (WP_B), U2.8 (VCC); also elsewhere on the board
